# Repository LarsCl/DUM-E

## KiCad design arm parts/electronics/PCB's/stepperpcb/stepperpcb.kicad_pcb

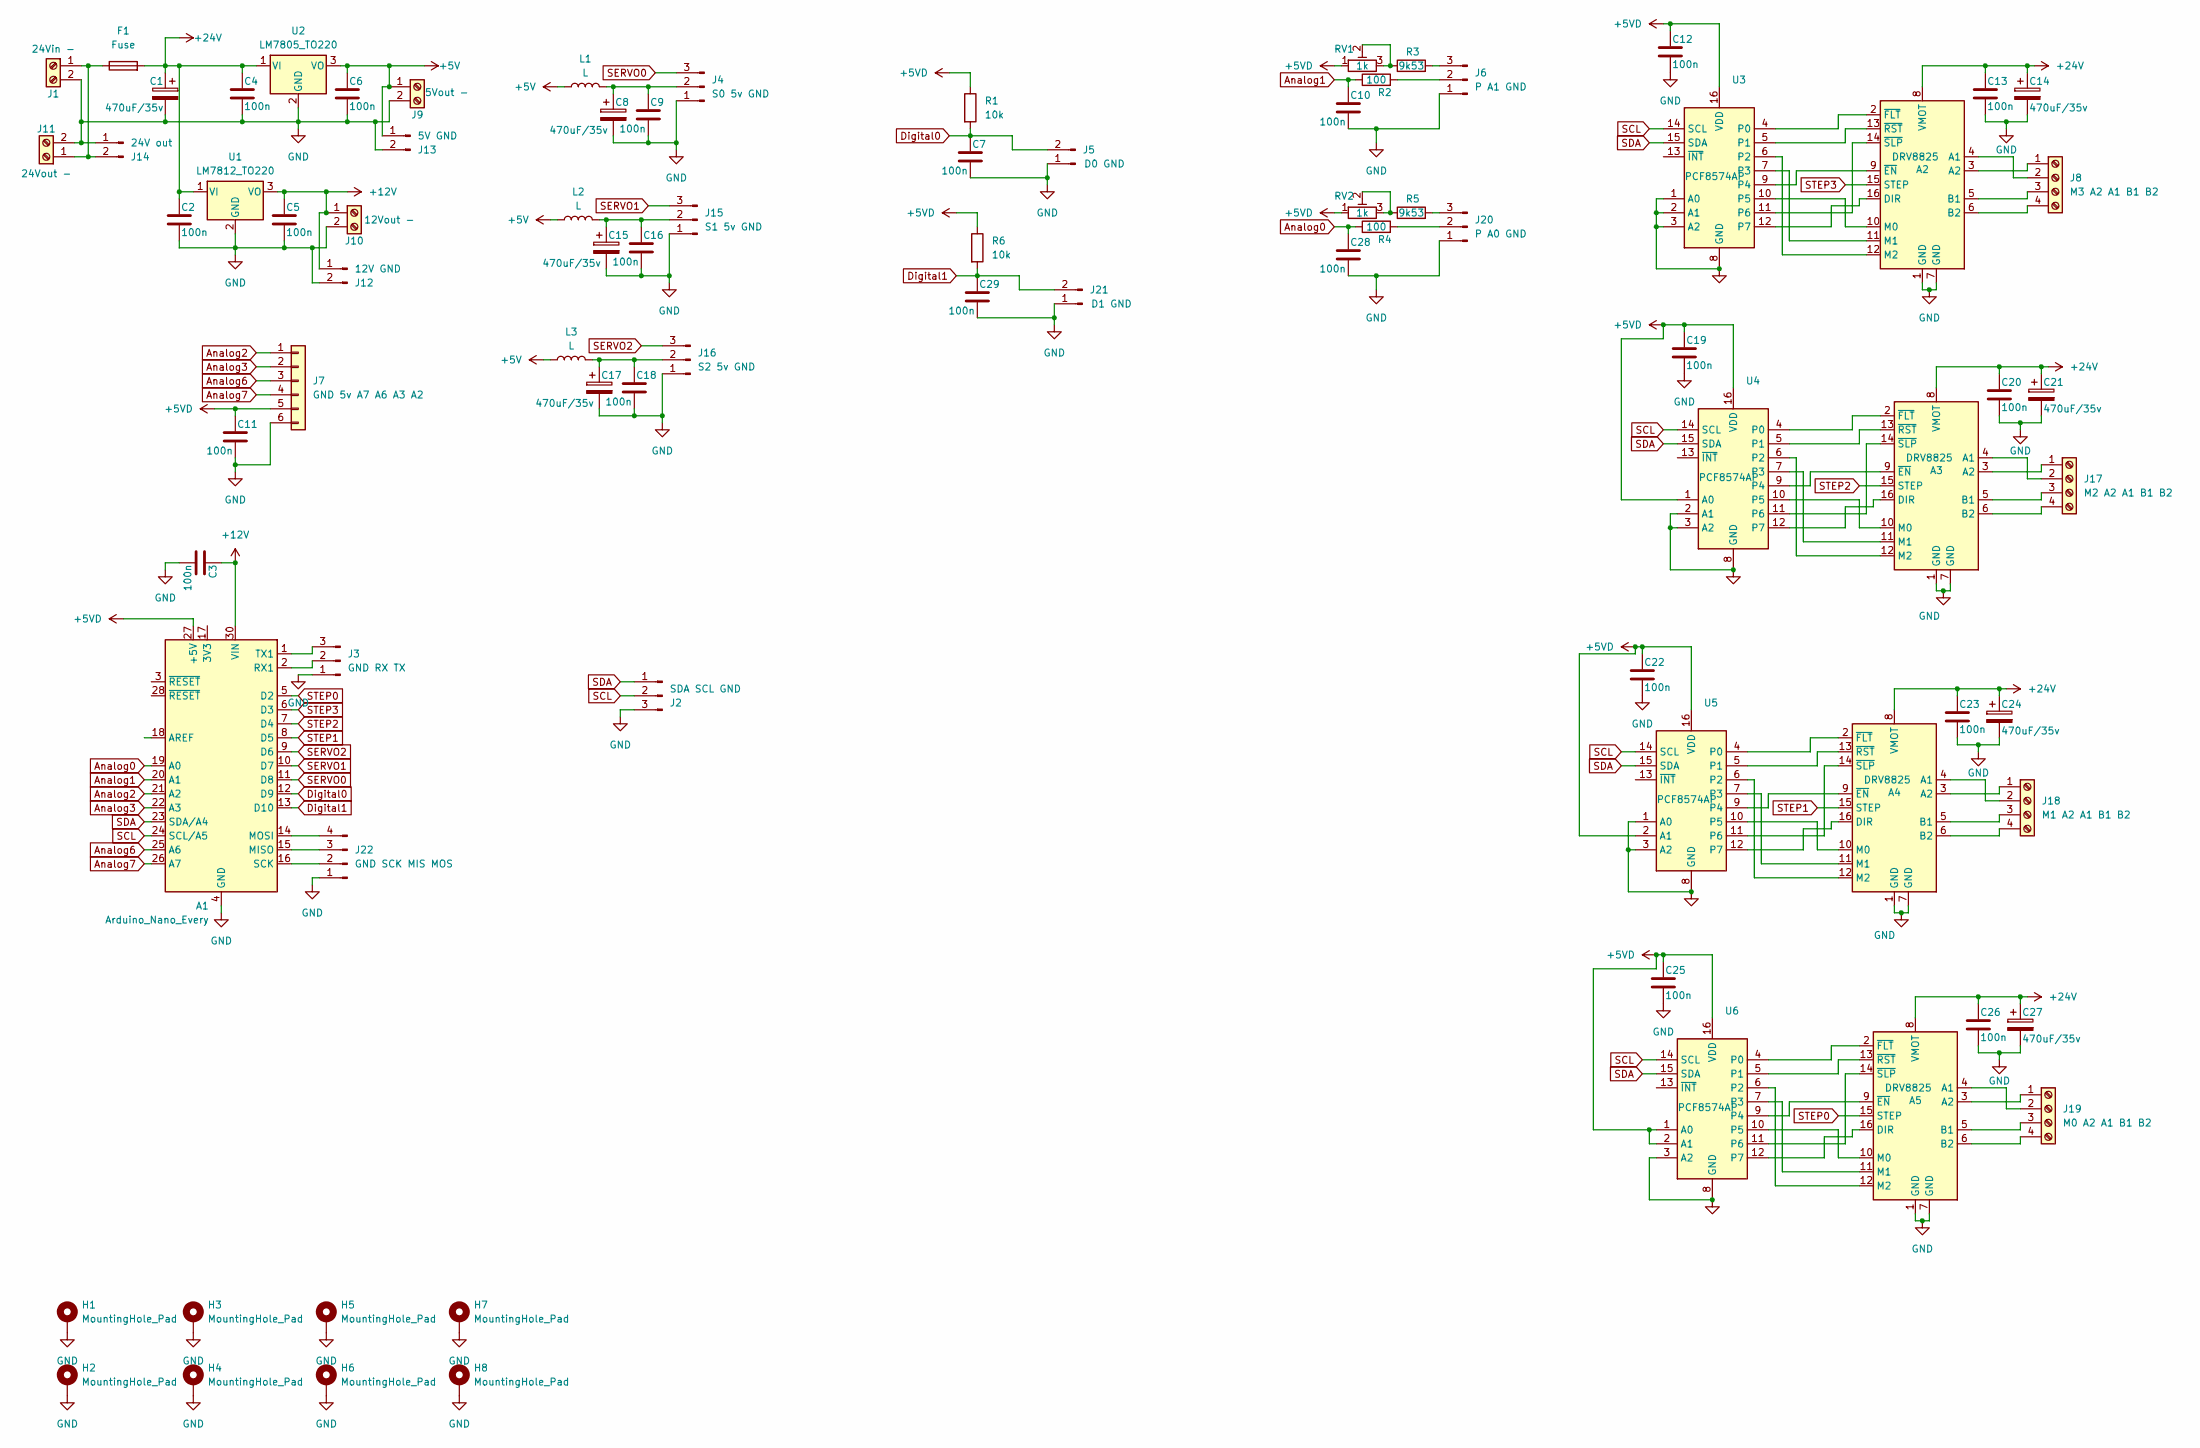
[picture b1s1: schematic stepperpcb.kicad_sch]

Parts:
A1: Arduino_Nano_Every; Arduino_Nano
A2, A3, A4, A5: DRV8825; Pololu_Breakout-16_15.2x20.3mm
C1, C8, C14, C15, C17, C21, C24, C27: 470uF/35v; C_Radial_D10.0mm_H12.5mm_P5.00mm
C2, C3, C4, C5, C6, C7, C9, C10, C11, C12, C13, C16, C18, C19, C20, C22, C23, C25, C26, C28, C29: 100n; C_1206_3216Metric_Pad1.33x1.80mm_HandSolder
F1: Fuse; Fuseholder_Cylinder-5x20mm_EATON_HBW_Vertical_Closed
H1, H2, H3, H4, H5, H6, H7, H8: MountingHole_Pad; MountingHole_3.2mm_M3_DIN965_Pad_TopBottom
J1: 24Vin -; TerminalBlock_Phoenix_MKDS-1,5-2-5.08_1x02_P5.08mm_Horizont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
J2: SDA SCL GND; PinHeader_1x03_P2.54mm_Vertical
J3: GND RX TX; PinHeader_1x03_P2.54mm_Vertical
J4: S0 5v GND; PinHeader_1x03_P2.54mm_Vertical
J5: D0 GND; PinHeader_1x02_P2.54mm_Vertical
J6: P A1 GND; PinHeader_1x03_P2.54mm_Vertical
J7: GND 5v A7 A6 A3 A2; PinHeader_1x06_P2.54mm_Vertical
J8: M3 A2 A1 B1 B2; TerminalBlock_Phoenix_MKDS-1,5-4-5.08_1x04_P5.08mm_Horizont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
J9: 5Vout -; TerminalBlock_Phoenix_MKDS-1,5-2-5.08_1x02_P5.08mm_Horizont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
J10: 12Vout -; TerminalBlock_Phoenix_MKDS-1,5-2-5.08_1x02_P5.08mm_Horizont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
J11: 24Vout -; TerminalBlock_Phoenix_MKDS-1,5-2-5.08_1x02_P5.08mm_Horizont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
J12: 12V GND; PinHeader_1x02_P2.54mm_Vertical
J13: 5V GND; PinHeader_1x02_P2.54mm_Vertical
J14: 24V out; PinHeader_1x02_P2.54mm_Vertical
J15: S1 5v GND; PinHeader_1x03_P2.54mm_Vertical
J16: S2 5v GND; PinHeader_1x03_P2.54mm_Vertical
J17: M2 A2 A1 B1 B2; TerminalBlock_Phoenix_MKDS-1,5-4-5.08_1x04_P5.08mm_Horizont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
J18: M1 A2 A1 B1 B2; TerminalBlock_Phoenix_MKDS-1,5-4-5.08_1x04_P5.08mm_Horizont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
J19: M0 A2 A1 B1 B2; TerminalBlock_Phoenix_MKDS-1,5-4-5.08_1x04_P5.08mm_Horizont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
J20: P A0 GND; PinHeader_1x03_P2.54mm_Vertical
J21: D1 GND; PinHeader_1x02_P2.54mm_Vertical
J22: GND SCK MIS MOS; PinHeader_1x04_P2.54mm_Vertical
L1, L2, L3: L; L_Axial_L12.0mm_D5.0mm_P15.24mm_Horizontal_Fastron_MISC
R1, R6: 10k; R_1206_3216Metric_Pad1.30x1.75mm_HandSolder
R2, R4: 100; R_1206_3216Metric_Pad1.30x1.75mm_HandSolder
R3, R5: 9k53; R_1206_3216Metric_Pad1.30x1.75mm_HandSolder
RV1, RV2: 1k; Potentiometer_Bourns_3296W_Vertical
U1: LM7812_TO220; TO-220-3_Vertical
U2: LM7805_TO220; TO-220-3_Vertical
U3, U4, U5, U6: PCF8574AP; DIP-16_W7.62mm

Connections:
+5V: C6.1, J9.1, J13.1, L1.1, L2.1, L3.1, U2.3 (VO)
+5VD: A1.27 (+5V), C11.1, C12.1, C19.1, C22.1, C25.1, J7.5, R1.1, R6.1, RV1.1, RV2.1, U3.16 (VDD), U4.1 (A0), U4.16 (VDD), U5.2 (A1), U5.16 (VDD), U6.1 (A0), U6.2 (A1), U6.16 (VDD)
+12V: A1.30 (VIN), C3.1, C5.1, J10.1, J12.1, U1.3 (VO)
+24V: A2.8 (VMOT), A3.8 (VMOT), A4.8 (VMOT), A5.8 (VMOT), C1.1, C2.1, C4.1, C13.1, C14.1, C20.1, C21.1, C23.1, C24.1, C26.1, C27.1, F1.2, U1.1 (VI), U2.1 (VI)
Analog0: A1.19 (A0), C28.1, R4.1
Analog1: A1.20 (A1), C10.1, R2.1
Analog2: A1.21 (A2), J7.1
Analog3: A1.22 (A3), J7.2
Analog6: A1.25 (A6), J7.3
Analog7: A1.26 (A7), J7.4
Digital0: A1.12 (D9), C7.1, J5.2, R1.2
Digital1: A1.13 (D10), C29.1, J21.2, R6.2
GND: A1.4 (GND), A1.29 (GND), A2.1 (GND), A2.7 (GND), A3.1 (GND), A3.7 (GND), A4.1 (GND), A4.7 (GND), A5.1 (GND), A5.7 (GND), C1.2, C2.2, C3.2, C4.2, C5.2, C6.2, C7.2, C8.2, C9.2, C10.2, C11.2, C12.2, C13.2, C14.2, C15.2, C16.2, C17.2, C18.2, C19.2, C20.2, C21.2, C22.2, C23.2, C24.2, C25.2, C26.2, C27.2, C28.2, C29.2, H1.1, H2.1, H3.1, H4.1, H5.1, H6.1, H7.1, H8.1, J1.2, J2.3, J3.1, J4.1, J5.1, J6.1, J7.6, J9.2, J10.2, J11.2, J12.2, J13.2, J14.1, J15.1, J16.1, J20.1, J21.1, J22.1, U1.2 (GND), U2.2 (GND), U3.1 (A0), U3.2 (A1), U3.3 (A2), U3.8 (GND), U4.2 (A1), U4.3 (A2), U4.8 (GND), U5.1 (A0), U5.3 (A2), U5.8 (GND), U6.3 (A2), U6.8 (GND)
unnamed: A1.15 (MISO), J22.3
unnamed: A1.14 (MOSI), J22.4
unnamed: A1.2 (RX1), J3.2
unnamed: A1.16 (SCK), J22.2
unnamed: A1.1 (TX1), J3.3
unnamed: A2.4 (A1), J8.2
unnamed: A2.3 (A2), J8.1
unnamed: A2.5 (B1), J8.3
unnamed: A2.6 (B2), J8.4
unnamed: A2.16 (DIR), U3.12 (P7)
unnamed: A2.10 (M0), U3.10 (P5)
unnamed: A2.11 (M1), U3.7 (P3)
unnamed: A2.12 (M2), U3.6 (P2)
unnamed: A2.9 (~EN), U3.9 (P4)
unnamed: A2.2 (~FLT), U3.4 (P0)
unnamed: A2.13 (~RST), U3.5 (P1)
unnamed: A2.14 (~SLP), U3.11 (P6)
unnamed: A3.4 (A1), J17.2
unnamed: A3.3 (A2), J17.1
unnamed: A3.5 (B1), J17.3
unnamed: A3.6 (B2), J17.4
unnamed: A3.16 (DIR), U4.12 (P7)
unnamed: A3.10 (M0), U4.10 (P5)
unnamed: A3.11 (M1), U4.7 (P3)
unnamed: A3.12 (M2), U4.6 (P2)
unnamed: A3.9 (~EN), U4.9 (P4)
unnamed: A3.2 (~FLT), U4.4 (P0)
unnamed: A3.13 (~RST), U4.5 (P1)
unnamed: A3.14 (~SLP), U4.11 (P6)
unnamed: A4.4 (A1), J18.2
unnamed: A4.3 (A2), J18.1
unnamed: A4.5 (B1), J18.3
unnamed: A4.6 (B2), J18.4
unnamed: A4.16 (DIR), U5.12 (P7)
unnamed: A4.10 (M0), U5.10 (P5)
unnamed: A4.11 (M1), U5.7 (P3)
unnamed: A4.12 (M2), U5.6 (P2)
unnamed: A4.9 (~EN), U5.9 (P4)
unnamed: A4.2 (~FLT), U5.4 (P0)
unnamed: A4.13 (~RST), U5.5 (P1)
unnamed: A4.14 (~SLP), U5.11 (P6)
unnamed: A5.4 (A1), J19.2
unnamed: A5.3 (A2), J19.1
unnamed: A5.5 (B1), J19.3
unnamed: A5.6 (B2), J19.4
unnamed: A5.16 (DIR), U6.12 (P7)
unnamed: A5.10 (M0), U6.10 (P5)
unnamed: A5.11 (M1), U6.7 (P3)
unnamed: A5.12 (M2), U6.6 (P2)
unnamed: A5.9 (~EN), U6.9 (P4)
unnamed: A5.2 (~FLT), U6.4 (P0)
unnamed: A5.13 (~RST), U6.5 (P1)
unnamed: A5.14 (~SLP), U6.11 (P6)
unnamed: F1.1, J1.1, J11.1, J14.2
unnamed: C8.1, C9.1, J4.2, L1.2
unnamed: J6.2, R2.2
unnamed: J6.3, R3.2
unnamed: C15.1, C16.1, J15.2, L2.2
unnamed: C17.1, C18.1, J16.2, L3.2
unnamed: J20.2, R4.2
unnamed: J20.3, R5.2
unnamed: R3.1, RV1.2, RV1.3
unnamed: R5.1, RV2.2, RV2.3
SCL: A1.24 (SCL/A5), J2.2, U3.14 (SCL), U4.14 (SCL), U5.14 (SCL), U6.14 (SCL)
SDA: A1.23 (SDA/A4), J2.1, U3.15 (SDA), U4.15 (SDA), U5.15 (SDA), U6.15 (SDA)
SERVO0: A1.11 (D8), J4.3
SERVO1: A1.10 (D7), J15.3
SERVO2: A1.9 (D6), J16.3
STEP0: A1.5 (D2), A5.15 (STEP)
STEP1: A1.8 (D5), A4.15 (STEP)
STEP2: A1.7 (D4), A3.15 (STEP)
STEP3: A1.6 (D3), A2.15 (STEP)

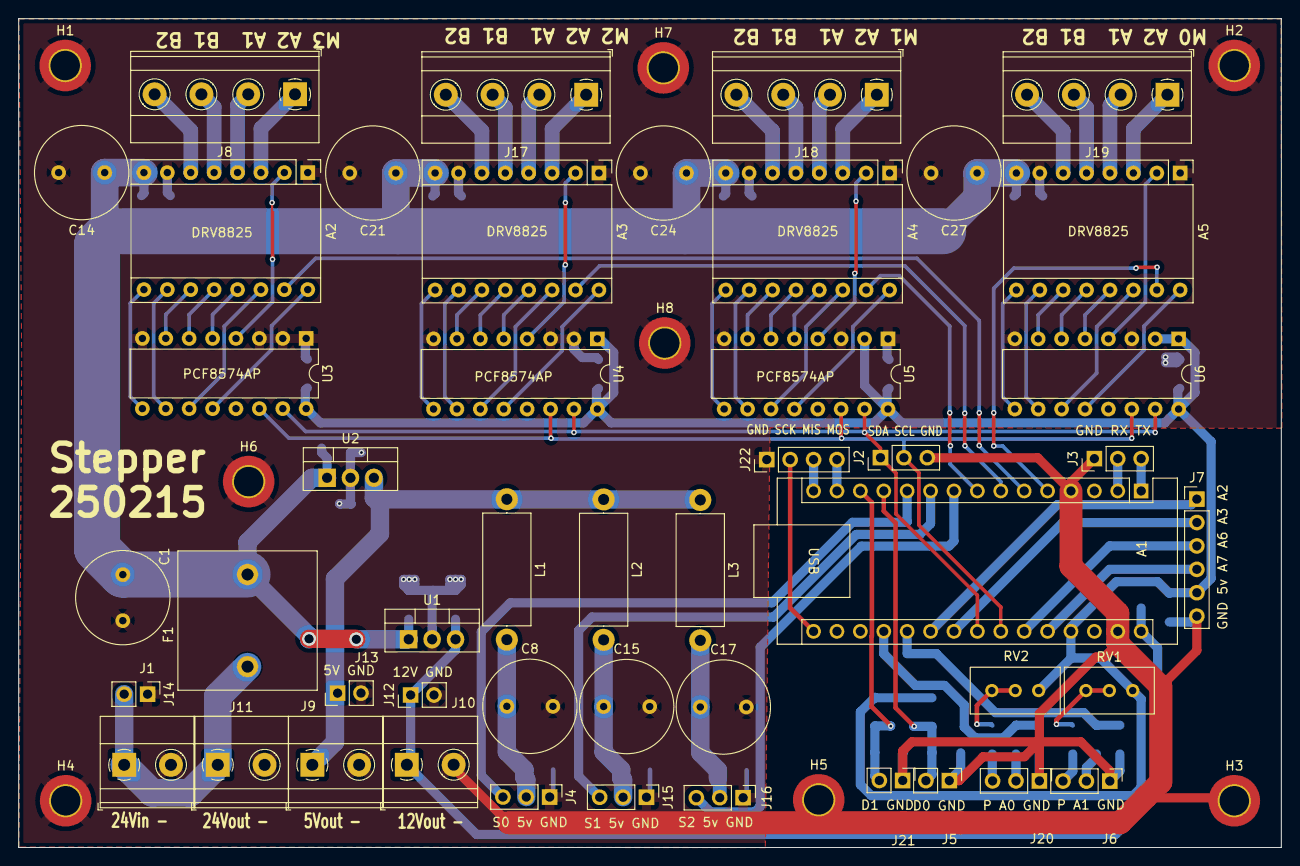
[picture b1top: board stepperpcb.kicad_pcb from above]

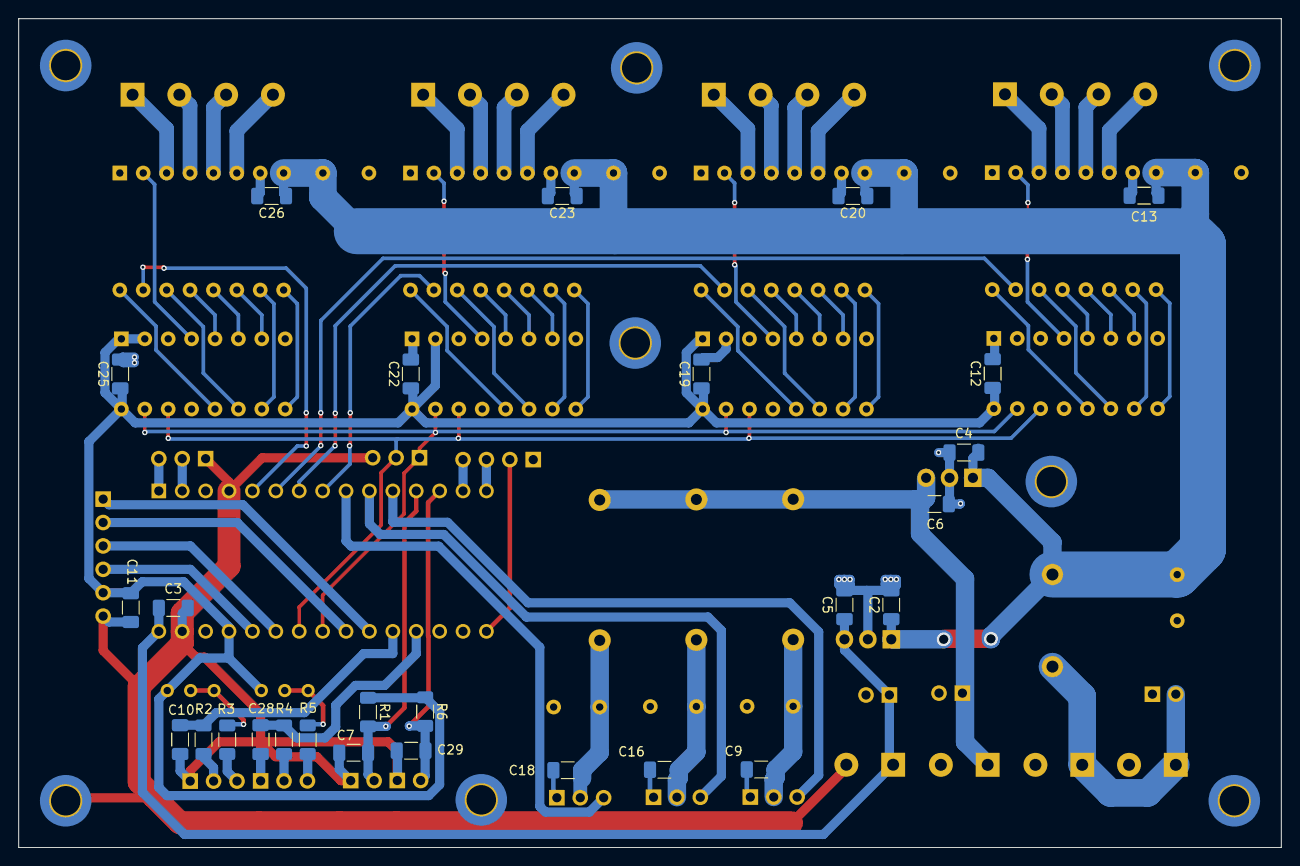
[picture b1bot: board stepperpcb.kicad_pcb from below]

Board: 2 copper layers, 137.1 x 90.0 mm, 82 parts (27 on the bottom side), 85 nets.

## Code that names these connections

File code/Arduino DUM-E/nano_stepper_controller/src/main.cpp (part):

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#define DIR_PIN 7

// Step pins for each motor (ARDUINO)
#define STEP0_PIN 2
#define STEP1_PIN 5
#define STEP2_PIN 4
#define STEP3_PIN 3

/* NANO PCBA nets*/
#define SERVO0 8
#define SERVO1 7
#define SERVO2 6
#define DIGITAL0 9
#define DIGITAL1 10

#define ANALOG0 0
#define ANALOG1 1
#define ANALOG2 2
#define ANALOG3 3
#define ANALOG6 6
#define ANALOG7 7

#define SERIAL_BUF_SIZE 32 /*bytes to hold in buf*/

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uint16_t adc0_initial_value;
uint16_t adc1_initial_value;

const uint8_t step_pins[PCF_COUNT] = {STEP3_PIN, STEP2_PIN, STEP1_PIN,
                                      STEP0_PIN};
const float gears_map[PCF_COUNT] = {motor_0_ratio, motor_1_ratio, motor_2_ratio,
                                    motor_3_ratio};

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  Serial.begin(115200);
  Wire.begin();

  pinMode(STEP0_PIN, OUTPUT);
  pinMode(STEP1_PIN, OUTPUT);
  pinMode(STEP2_PIN, OUTPUT);
  pinMode(STEP3_PIN, OUTPUT);

  pinMode(SERVO0, OUTPUT);
  pinMode(SERVO1, OUTPUT);
  pinMode(SERVO2, OUTPUT);
  pinMode(DIGITAL0, OUTPUT);
  pinMode(DIGITAL1, OUTPUT);

  digitalWrite(STEP0_PIN, LOW);
  digitalWrite(STEP1_PIN, LOW);
  digitalWrite(STEP2_PIN, LOW);
  digitalWrite(STEP3_PIN, LOW);

  digitalWrite(SERVO0, LOW);
  digitalWrite(SERVO1, LOW);
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
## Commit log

2025-02-24 first
2025-02-24 created space
    added library and setup
2025-02-25 Steppermotor rotation test
    added quick gpt code and added details to og code
2025-02-25 Update gpt code
    this is as basic as it gets, cant wait to test tomorrow
2025-02-25 plop
2025-02-25 pc sync
2025-02-25 deleted the old libs and made some arduino code
2025-02-26 updated mechanical assembly
2025-02-26 removed automatic kicad backup commits as project is tracked by git
2025-02-26 Added gitiknore to ignore locally generated kicad backup files from being added to the commits
2025-02-26 Removed a dot inside .gitignore file
2025-02-26 Removed a dot inside .gitignore
2025-02-27 Added .lck files to gitignore as WIP kicad schematics generate them.
2025-02-27 updated pulley to 120 teeth
2025-02-27 Added comments for extra description in KiCAD schematic, made io description
2025-02-27 new arduino angle to steps code
2025-02-28 updated and added some parts
2025-03-01 WIP: Made platformIO project with fixed PCF control
2025-03-10 Added -Wno-unused-variable buildflag, reformatted file to correct curly bracket format, added extra motor control functions, wrote down operation of stepper motor control state machine.
2025-03-11 sepperated code in multpiple files
2025-03-11 Added small mechanical components
    For cable management and securing
2025-03-11 working without whining
2025-03-11 extra pullys
2025-03-11 code
2025-03-11 Filled in stepper motor control loop, added rpm to step microsecond period macro, changed rotation and acceleration velocity vals, added extra struct members toggle time, software control blocking fl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
2025-03-12 odrvtest
2025-03-13 Optimized used struct members for less conversion. Added logic for acceleration calculation on per-step basis by function motion_profiler. Changed motor_control_loop for only executing step pulses. A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
2025-03-13 Added comments within motion profiler
2025-03-13 Slight bugfix
2025-03-13 Another bugfix
2025-03-13 all motors turning
2025-03-13 initial commit of a basic ROS project
    Decision made to use Python instead of C++
2025-03-13 full motor control with basic serial input
2025-03-14 WIP remote backup
2025-03-14 WIP debug checkpoint.
2025-03-14 Demo working accelo with fixed major bugs
2025-03-14 Endeffector rotation demo
2025-03-16 Working acceleration
2025-03-16 Bugfixes, cleanup.
2025-03-16 Added a higer optimalization flag to compiler flags. Added automatic acceleration and max RPM conversion when changing motor microstep config.
2025-03-16 Parallel movement demo, control using decadegrees
2025-03-16 Started synchronisation code
2025-03-18 WIP synchromizer re-written
2025-03-19 cad update
2025-03-19 smarty deployment
2025-03-19 URDF YIPPIEEEEE
2025-03-19 added nano every build target
2025-03-19 WIP code: fixed scaler code
2025-03-19 Applied some bugfixes and optimalisations
2025-03-20 Rotation demo OK!
2025-03-20 up & down demo mode
2025-03-21 Added upload limits to support weaker and sensitive arduino nano's
2025-03-21 added_the_smarty_configs
2025-03-21 removed spaces
2025-03-25 urdf stuff
2025-03-25 Removed (assumed) accidental re-commits of files
2025-03-25 Change rate/velocity setting function args to floats, removed modifying of accel/velo rates at setup. Changed the test code demo for movement speed calibration. Modified set_stepper rate and set_step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
2025-03-25 Changed datatypes of apply pose to support negative angles. Default position starts from 0 degree 0 step SP.
2025-03-25 Added serial command handler, package capturing and applying a pose through serial comms.
2025-03-27 WIP, serial package extensions and gear ratio calculation bugfixes
2025-03-27 Added defines for easy array number use of motors
2025-03-27 Cleaned up some commented out code. Minor operation changes.
2025-03-27 Changed default fullstep, added homing logic, added start homing function, deleted test code, added a accelo calculation bugfix, added changed packet processing logic, added motor config function.
2025-03-27 Added start homing as a package entry
2025-03-28 WIP bugfix testing code
2025-03-28 Confirmed gear ratio bugfix, swapped base angle setpoint at process packet. Code still has debug overwrites of HOMING.
2025-03-31 added cmd's 4 and 5
2025-04-01 Unfkd the calculations for current velocity and angles
2025-04-01 Fixed send position
2025-04-02 WIP, direct control hacdk
2025-04-03 added hardware node and propper launch file for Moveit2
2025-04-22 Update hardware_node.py
    removed '1' before a comment which made the code not run
